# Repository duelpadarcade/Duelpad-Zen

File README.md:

## **Duelpad Zen**

Duelpad zen is a split-layout all-button controller, which is based on GP2040-CE projects. So it inherits the features, and is also added with something new.

## **Features**

- A navigating stick used with a humble UI,which can change the working status of the controller.
- Select from 13 input modes including X-Input, Nintendo Switch, Playstation 4/5, Xbox One, D-Input, and Keyboard
- Input latency average of 0.76ms in Xinput and 0.90ms for Playstation 5.
- Multiple SOCD cleaning modes - Up Priority (a.k.a. Stickless), Neutral, and Second Input Priority.
- Left and Right stick emulation via D-pad inputs as well as dedicated toggle switches.
- Dual direction via D-pad + LS/RS.
- Reversed input via a button.
- [Turbo and Turbo LED](https://gp2040-ce.info/add-ons/turbo) with selectable speed
- Per-button RGB LED support.
- PWM Player indicator LED support (XInput only).
- Multiple LED profiles support.
- Support for 128x64 monochrome I2C displays - SSD1306, SH1106, and SH1107 compatible.
- Custom startup splash screen and easy image upload via web configuration.
- Support for passive buzzer speaker (3v or 5v).
- [Built-in, embedded web configuration](https://gp2040-ce.info/web-configurator) - No download required!
- A bunch of RGB lights run by an extra MCU

## Support

We welcome anyone with ideas or issues to join us:

Official Website: www.duelpad.com

Discord Server:[DUELPAD](https://discord.gg/BXeWntUJ8B)

## Acknowledgements

This project is based on the excellent work of GP2040-CE team([Contributors to OpenStickCommunity/GP2040-CE · GitHub](https://github.com/OpenStickCommunity/GP2040-CE/graphs/contributors))

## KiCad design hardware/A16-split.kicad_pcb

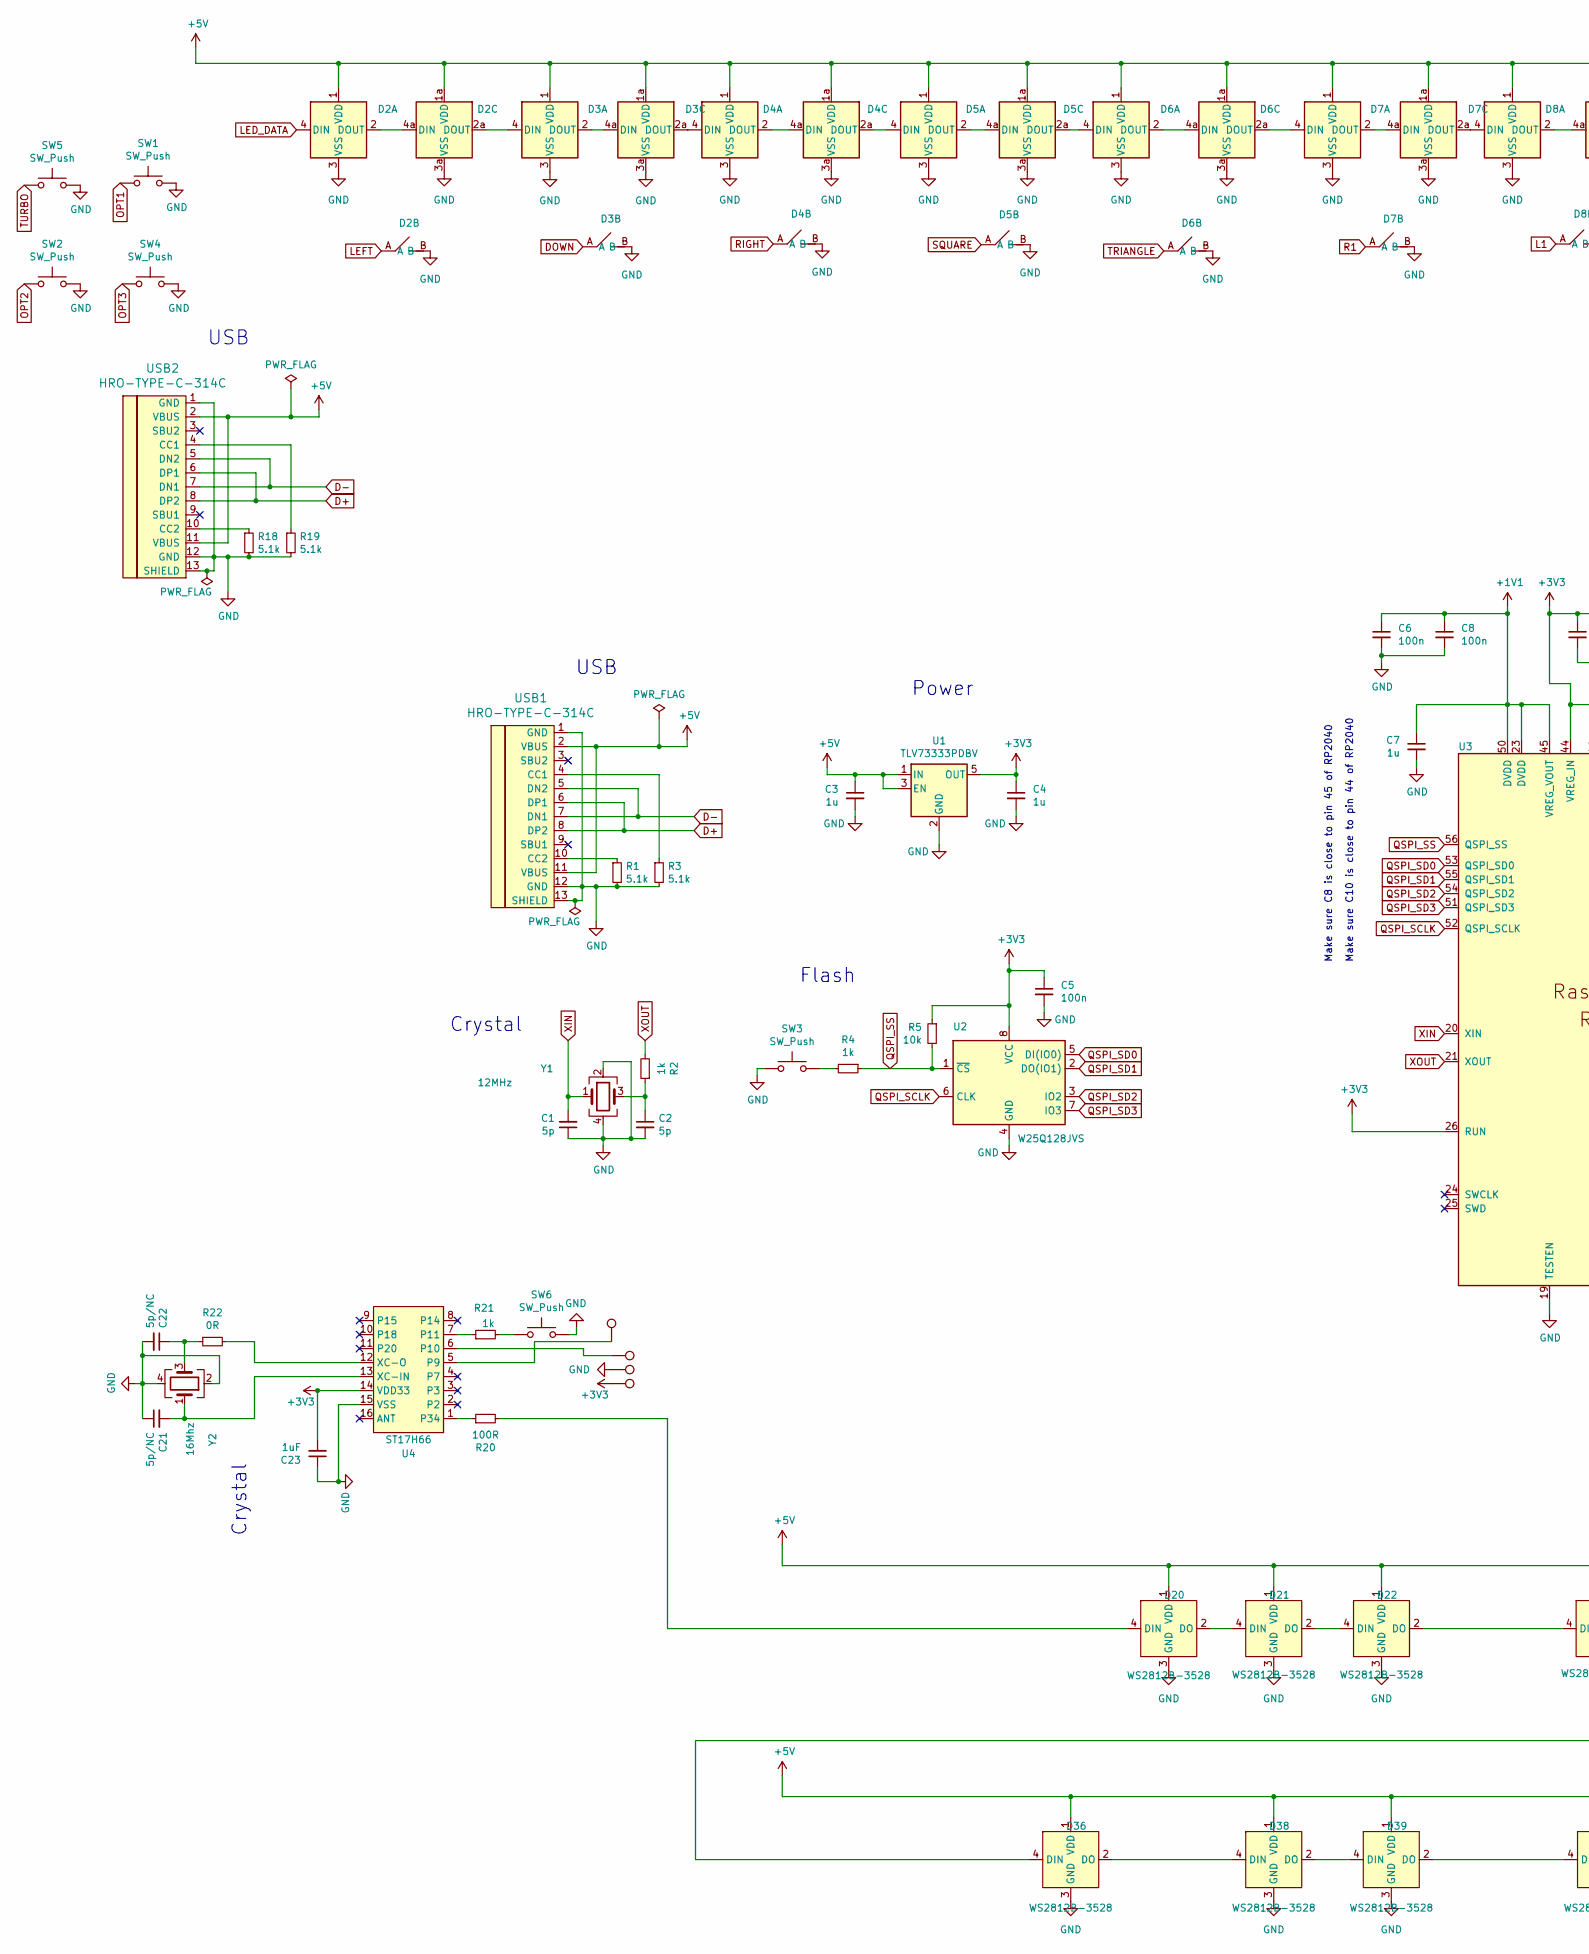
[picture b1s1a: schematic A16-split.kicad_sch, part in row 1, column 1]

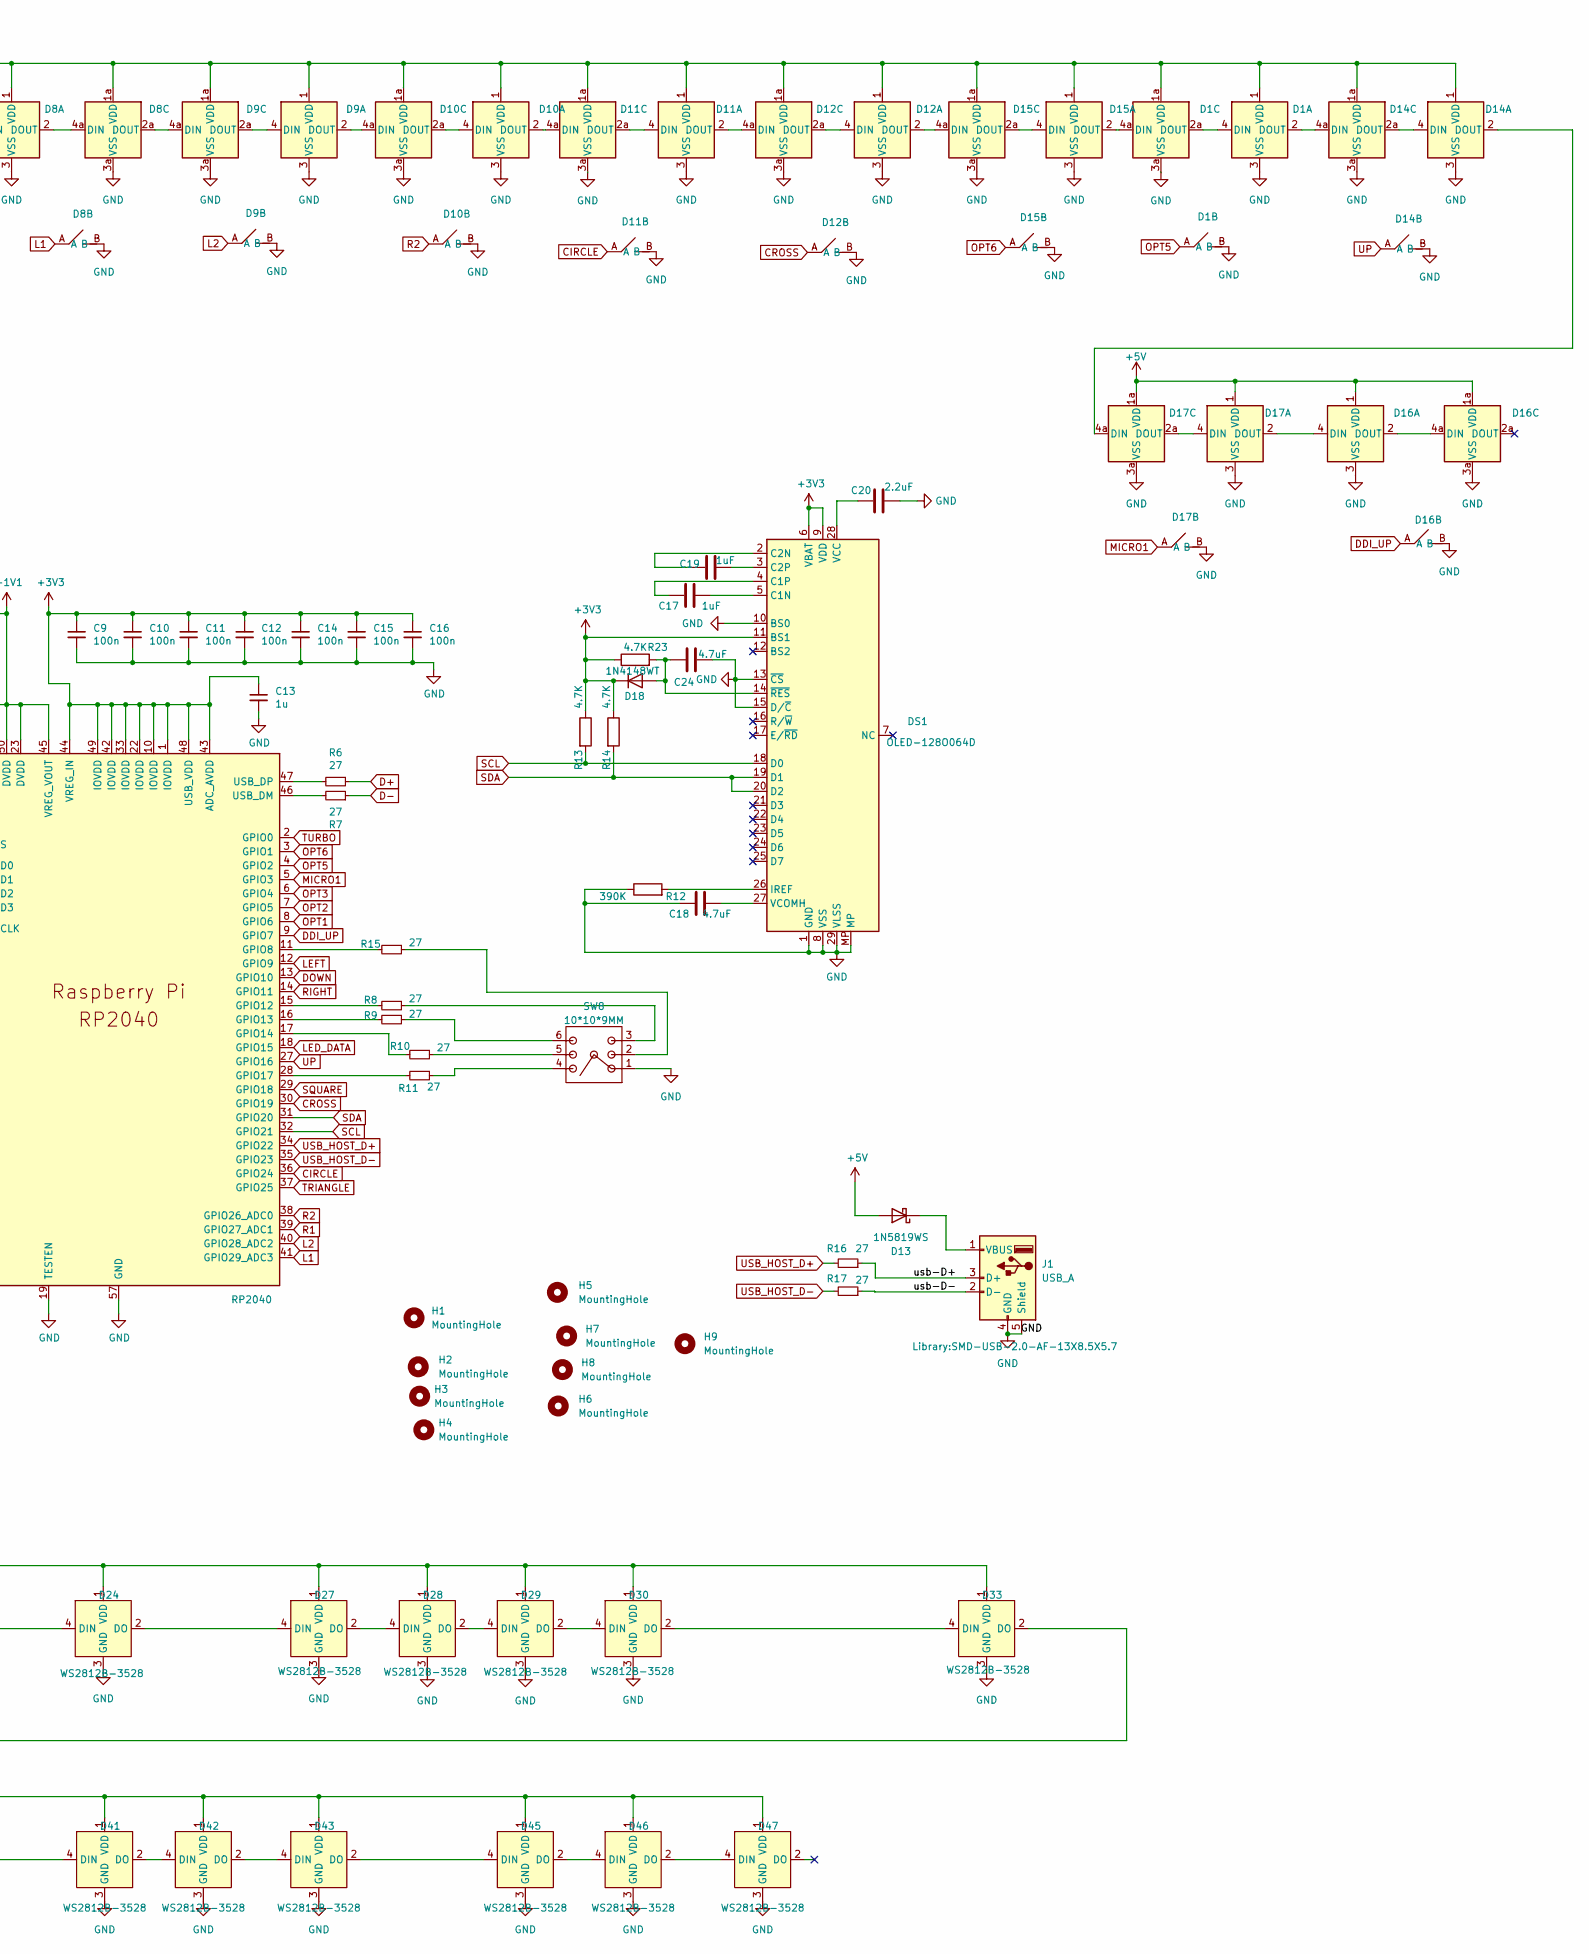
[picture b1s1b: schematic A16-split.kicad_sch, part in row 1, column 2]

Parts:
C1, C2: 5p; C_0402_1005Metric; LCSC C1570
C3, C4, C7, C13: 1u; C_0402_1005Metric; LCSC C52923
C5, C6, C8, C9, C10, C11, C12, C14, C15, C16: 100n; C_0402_1005Metric; LCSC C1525
C17, C19: 1uF; C_0402_1005Metric
C18, C24: 4.7uF; C_0603_1608Metric
C20: 2.2uF; C_0603_1608Metric
C21, C22: 5p/NC; C_0402_1005Metric; LCSC C1570
C23: 1uF; C_0402_1005Metric; LCSC C52923
D1, D2, D3, D4, D5, D6, D7, D8, D9, D10, D11, D12, D14, D15, D16, D17: GATERON_KB_HOTSWAP_WS2812B; gateron_Kailh_PG1353_2LED-5.1MM
D13: 1N5819WS; D_SOD-323
D18: 1N4148WT; D_SOD-523
D20, D21, D22, D24, D27, D28, D29, D30, D33, D36, D38, D39, D41, D42, D43, D45, D46, D47: WS2812B-3528; SMD-LED-WS2812B-3528
DS1: OLED-128O064D; Flatbox_OLED_096-1
H1, H2, H3, H4, H5, H6, H7, H8, H9: MountingHole; MountingHole_3.15mm_M6
J1: USB_A; SMD-USB-2.0-AF-13X8.5X5.7
R1, R3, R18, R19: 5.1k; R_0402_1005Metric; LCSC C25905
R2, R4, R21: 1k; R_0402_1005Metric; LCSC C11702
R5: 10k; R_0402_1005Metric; LCSC C25744
R6, R7, R8, R9, R10, R11, R15, R16, R17: 27; R_0402_1005Metric; LCSC C138021
R12: 390K; R_0402_1005Metric
R13, R14, R23: 4.7K; R_0402_1005Metric
R20: 100R; R_0402_1005Metric; LCSC C11702
R22: 0R; R_0402_1005Metric; LCSC C11702
SW1, SW2, SW4, SW5: SW_Push; SW_Push_1P1T_NO_6x6mm_H5mm
SW3, SW6: SW_Push; SW_Push_1P1T_NO_6x6mm_H5mm; LCSC C271750
SW8: 10*10*9MM; TSX103G901-10x10
TP1, TP2, TP3, TP4: TestPoint; TestPoint_Pad_D1.5mm
U1: TLV73333PDBV; SOT-23-5; LCSC C134139
U2: W25Q128JVS; SOIC-8_5.23x5.23mm_P1.27mm; LCSC C97521
U3: RP2040; RP2040-QFN-56; LCSC C2040
U4: ST17H66; TSSOP-16_4.4x5mm_P0.65mm
USB1, USB2: HRO-TYPE-C-314C; HRO-TYPE-MC-314C-4P16; LCSC C165948
Y1: 12MHz; Crystal_SMD_3225-4Pin_3.2x2.5mm; LCSC C9002
Y2: 16Mhz; Crystal_SMD_3225-4Pin_3.2x2.5mm; LCSC C9002

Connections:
+1V1: C6.1, C7.1, C8.1, U3.23 (DVDD), U3.45 (VREG_VOUT), U3.50 (DVDD)
+3V3: C4.1, C5.1, C9.1, C10.1, C11.1, C12.1, C13.1, C14.1, C15.1, C16.1, C23.2, D18.1 (K), DS1.6 (VBAT), DS1.9 (VDD), DS1.11 (BS1), R5.1, R13.1, R14.1, R23.1, TP4.1, U1.5 (OUT), U2.8 (VCC), U3.1 (IOVDD), U3.10 (IOVDD), U3.22 (IOVDD), U3.26 (RUN), U3.33 (IOVDD), U3.42 (IOVDD), U3.43 (ADC_AVDD), U3.44 (VREG_IN), U3.48 (USB_VDD), U3.49 (IOVDD), U4.14 (VDD33)
+5V: C3.1, D1.1 (VDD), D1.1a (VDD), D2.1 (VDD), D2.1a (VDD), D3.1 (VDD), D3.1a (VDD), D4.1 (VDD), D4.1a (VDD), D5.1 (VDD), D5.1a (VDD), D6.1 (VDD), D6.1a (VDD), D7.1 (VDD), D7.1a (VDD), D8.1 (VDD), D8.1a (VDD), D9.1 (VDD), D9.1a (VDD), D10.1 (VDD), D10.1a (VDD), D11.1 (VDD), D11.1a (VDD), D12.1 (VDD), D12.1a (VDD), D13.2 (A), D14.1 (VDD), D14.1a (VDD), D15.1 (VDD), D15.1a (VDD), D16.1 (VDD), D16.1a (VDD), D17.1 (VDD), D17.1a (VDD), D20.1 (VDD), D21.1 (VDD), D22.1 (VDD), D24.1 (VDD), D27.1 (VDD), D28.1 (VDD), D29.1 (VDD), D30.1 (VDD), D33.1 (VDD), D36.1 (VDD), D38.1 (VDD), D39.1 (VDD), D41.1 (VDD), D42.1 (VDD), D43.1 (VDD), D45.1 (VDD), D46.1 (VDD), D47.1 (VDD), U1.1 (IN), U1.3 (EN), USB1.2 (VBUS), USB1.11 (VBUS), USB2.2 (VBUS), USB2.11 (VBUS)
/usb-D+: J1.3 (D+), R16.1
/usb-D-: J1.2 (D-), R17.1
CIRCLE: D11.A, U3.36 (GPIO24)
CROSS: D12.A, U3.30 (GPIO19)
D+: R6.1, USB1.6 (DP1), USB1.8 (DP2), USB2.6 (DP1), USB2.8 (DP2)
D-: R7.1, USB1.5 (DN2), USB1.7 (DN1), USB2.5 (DN2), USB2.7 (DN1)
DDI_UP: D16.A, U3.9 (GPIO7)
DOWN: D3.A, U3.13 (GPIO10)
GND: C1.1, C2.2, C3.2, C4.2, C5.2, C6.2, C7.2, C8.2, C9.2, C10.2, C11.2, C12.2, C13.2, C14.2, C15.2, C16.2, C18.1, C20.2, C21.1, C22.2, C23.1, C24.2, D1.3 (VSS), D1.3a (VSS), D1.B, D2.3 (VSS), D2.3a (VSS), D2.B, D3.3 (VSS), D3.3a (VSS), D3.B, D4.3 (VSS), D4.3a (VSS), D4.B, D5.3 (VSS), D5.3a (VSS), D5.B, D6.3 (VSS), D6.3a (VSS), D6.B, D7.3 (VSS), D7.3a (VSS), D7.B, D8.3 (VSS), D8.3a (VSS), D8.B, D9.3 (VSS), D9.3a (VSS), D9.B, D10.3 (VSS), D10.3a (VSS), D10.B, D11.3 (VSS), D11.3a (VSS), D11.B, D12.3 (VSS), D12.3a (VSS), D12.B, D14.3 (VSS), D14.3a (VSS), D14.B, D15.3 (VSS), D15.3a (VSS), D15.B, D16.3 (VSS), D16.3a (VSS), D16.B, D17.3 (VSS), D17.3a (VSS), D17.B, D20.3 (GND), D21.3 (GND), D22.3 (GND), D24.3 (GND), D27.3 (GND), D28.3 (GND), D29.3 (GND), D30.3 (GND), D33.3 (GND), D36.3 (GND), D38.3 (GND), D39.3 (GND), D41.3 (GND), D42.3 (GND), D43.3 (GND), D45.3 (GND), D46.3 (GND), D47.3 (GND), DS1.1 (GND), DS1.8 (VSS), DS1.10 (BS0), DS1.13 (~CS), DS1.15 (D/~C), DS1.29 (VLSS), DS1.30 (GND), DS1.MP, J1.4 (GND), J1.5 (Shield), R1.2, R3.2, R12.1, R18.2, R19.2, SW1.2, SW2.2, SW3.1, SW4.2, SW5.2, SW6.2, SW8.1, TP3.1, U1.2 (GND), U2.4 (GND), U3.19 (TESTEN), U3.57 (GND), U4.15 (VSS), USB1.1 (GND), USB1.12 (GND), USB1.13 (SHIELD), USB2.1 (GND), USB2.12 (GND), USB2.13 (SHIELD), Y1.2, Y1.4, Y2.2, Y2.4
L1: D8.A, U3.41 (GPIO29_ADC3)
L2: D9.A, U3.40 (GPIO28_ADC2)
LED_DATA: D2.4 (DIN), U3.18 (GPIO15)
LEFT: D2.A, U3.12 (GPIO9)
MICRO1: D17.A, U3.5 (GPIO3)
unnamed: C2.1, R2.1, Y1.3
unnamed: C22.1, R22.1, Y2.3
unnamed: D1.2a (DOUT), D1.4 (DIN)
unnamed: D2.2 (DOUT), D2.4a (DIN)
unnamed: D2.2a (DOUT), D3.4 (DIN)
unnamed: D3.2 (DOUT), D3.4a (DIN)
unnamed: D3.2a (DOUT), D4.4 (DIN)
unnamed: D4.2 (DOUT), D4.4a (DIN)
unnamed: D4.2a (DOUT), D5.4 (DIN)
unnamed: D5.2 (DOUT), D5.4a (DIN)
unnamed: D5.2a (DOUT), D6.4 (DIN)
unnamed: D6.2 (DOUT), D6.4a (DIN)
unnamed: D6.2a (DOUT), D7.4 (DIN)
unnamed: D7.2 (DOUT), D7.4a (DIN)
unnamed: D7.2a (DOUT), D8.4 (DIN)
unnamed: D8.2 (DOUT), D8.4a (DIN)
unnamed: D8.2a (DOUT), D9.4a (DIN)
unnamed: D9.2a (DOUT), D9.4 (DIN)
unnamed: D10.2a (DOUT), D10.4 (DIN)
unnamed: D10.2 (DOUT), D11.4a (DIN)
unnamed: D9.2 (DOUT), D10.4a (DIN)
unnamed: D11.2a (DOUT), D11.4 (DIN)
unnamed: D11.2 (DOUT), D12.4a (DIN)
unnamed: D12.2a (DOUT), D12.4 (DIN)
unnamed: D12.2 (DOUT), D15.4a (DIN)
unnamed: D13.1 (K), J1.1 (VBUS)
unnamed: D14.2a (DOUT), D14.4 (DIN)
unnamed: D14.2 (DOUT), D17.4a (DIN)
unnamed: D1.2 (DOUT), D14.4a (DIN)
unnamed: D15.2a (DOUT), D15.4 (DIN)
unnamed: D1.4a (DIN), D15.2 (DOUT)
unnamed: D16.4 (DIN), D17.2 (DOUT)
unnamed: D16.2 (DOUT), D16.4a (DIN)
unnamed: D17.2a (DOUT), D17.4 (DIN)
unnamed: C24.1, D18.2 (A), DS1.14 (~RES), R23.2
unnamed: D20.4 (DIN), R20.2
unnamed: D20.2 (DO), D21.4 (DIN)
unnamed: D21.2 (DO), D22.4 (DIN)
unnamed: D22.2 (DO), D24.4 (DIN)
unnamed: D24.2 (DO), D27.4 (DIN)
unnamed: D27.2 (DO), D28.4 (DIN)
unnamed: D28.2 (DO), D29.4 (DIN)
unnamed: D29.2 (DO), D30.4 (DIN)
unnamed: D30.2 (DO), D33.4 (DIN)
unnamed: D33.2 (DO), D36.4 (DIN)
unnamed: D36.2 (DO), D38.4 (DIN)
unnamed: D38.2 (DO), D39.4 (DIN)
unnamed: D39.2 (DO), D41.4 (DIN)
unnamed: D41.2 (DO), D42.4 (DIN)
unnamed: D42.2 (DO), D43.4 (DIN)
unnamed: D43.2 (DO), D45.4 (DIN)
unnamed: D45.2 (DO), D46.4 (DIN)
unnamed: D46.2 (DO), D47.4 (DIN)
unnamed: C17.2, DS1.5 (C1N)
unnamed: C17.1, DS1.4 (C1P)
unnamed: C19.1, DS1.2 (C2N)
unnamed: C19.2, DS1.3 (C2P)
unnamed: DS1.26 (IREF), R12.2
unnamed: C20.1, DS1.28 (VCC)
unnamed: C18.2, DS1.27 (VCOMH)
unnamed: R4.2, SW3.2
unnamed: R8.1, SW8.3
unnamed: R9.1, SW8.6
unnamed: R10.1, SW8.5
unnamed: R11.1, SW8.4
unnamed: R15.1, SW8.2
unnamed: R21.2, SW6.1
unnamed: R15.2, U3.11 (GPIO8)
unnamed: R8.2, U3.15 (GPIO12)
unnamed: R9.2, U3.16 (GPIO13)
unnamed: R10.2, U3.17 (GPIO14)
unnamed: R11.2, U3.28 (GPIO17)
unnamed: R7.2, U3.46 (USB_DM)
unnamed: R6.2, U3.47 (USB_DP)
unnamed: TP1.1, U4.5 (P9)
unnamed: TP2.1, U4.6 (P10)
unnamed: R21.1, U4.7 (P11)
unnamed: R20.1, U4.1 (P34)
unnamed: C21.2, U4.13 (XC-IN), Y2.1
unnamed: R22.2, U4.12 (XC-O)
unnamed: R3.1, USB1.4 (CC1)
unnamed: R1.1, USB1.10 (CC2)
unnamed: R19.1, USB2.4 (CC1)
unnamed: R18.1, USB2.10 (CC2)
OPT1: SW1.1, U3.8 (GPIO6)
OPT2: SW2.1, U3.7 (GPIO5)
OPT3: SW4.1, U3.6 (GPIO4)
OPT5: D1.A, U3.4 (GPIO2)
OPT6: D15.A, U3.3 (GPIO1)
QSPI_SCLK: U2.6 (CLK), U3.52 (QSPI_SCLK)
QSPI_SD0: U2.5 (DI(IO0)), U3.53 (QSPI_SD0)
QSPI_SD1: U2.2 (DO(IO1)), U3.55 (QSPI_SD1)
QSPI_SD2: U2.3 (IO2), U3.54 (QSPI_SD2)
QSPI_SD3: U2.7 (IO3), U3.51 (QSPI_SD3)
QSPI_SS: R4.1, R5.2, U2.1 (~CS), U3.56 (QSPI_SS)
R1: D7.A, U3.39 (GPIO27_ADC1)
R2: D10.A, U3.38 (GPIO26_ADC0)
RIGHT: D4.A, U3.14 (GPIO11)
SCL: DS1.18 (D0), R13.2, U3.32 (GPIO21)
SDA: DS1.19 (D1), DS1.20 (D2), R14.2, U3.31 (GPIO20)
SQUARE: D5.A, U3.29 (GPIO18)
TRIANGLE: D6.A, U3.37 (GPIO25)
TURBO: SW5.1, U3.2 (GPIO0)
UP: D14.A, U3.27 (GPIO16)
USB_HOST_D+: R16.2, U3.34 (GPIO22)
USB_HOST_D-: R17.2, U3.35 (GPIO23)
XIN: C1.2, U3.20 (XIN), Y1.1
XOUT: R2.2, U3.21 (XOUT)

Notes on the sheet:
USB
Make sure C10 is close to pin 44 of RP2040
Crystal
Flash
Power
Make sure C8 is close to pin 45 of RP2040

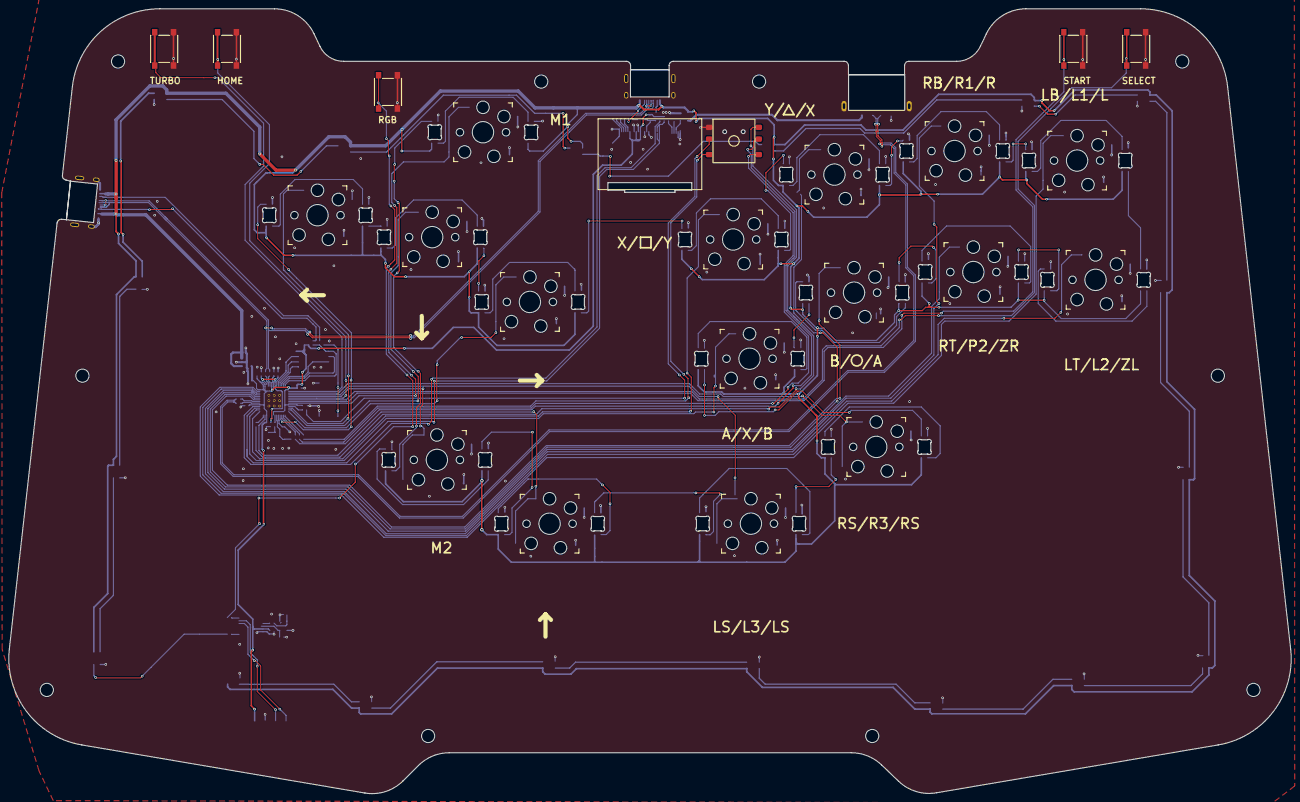
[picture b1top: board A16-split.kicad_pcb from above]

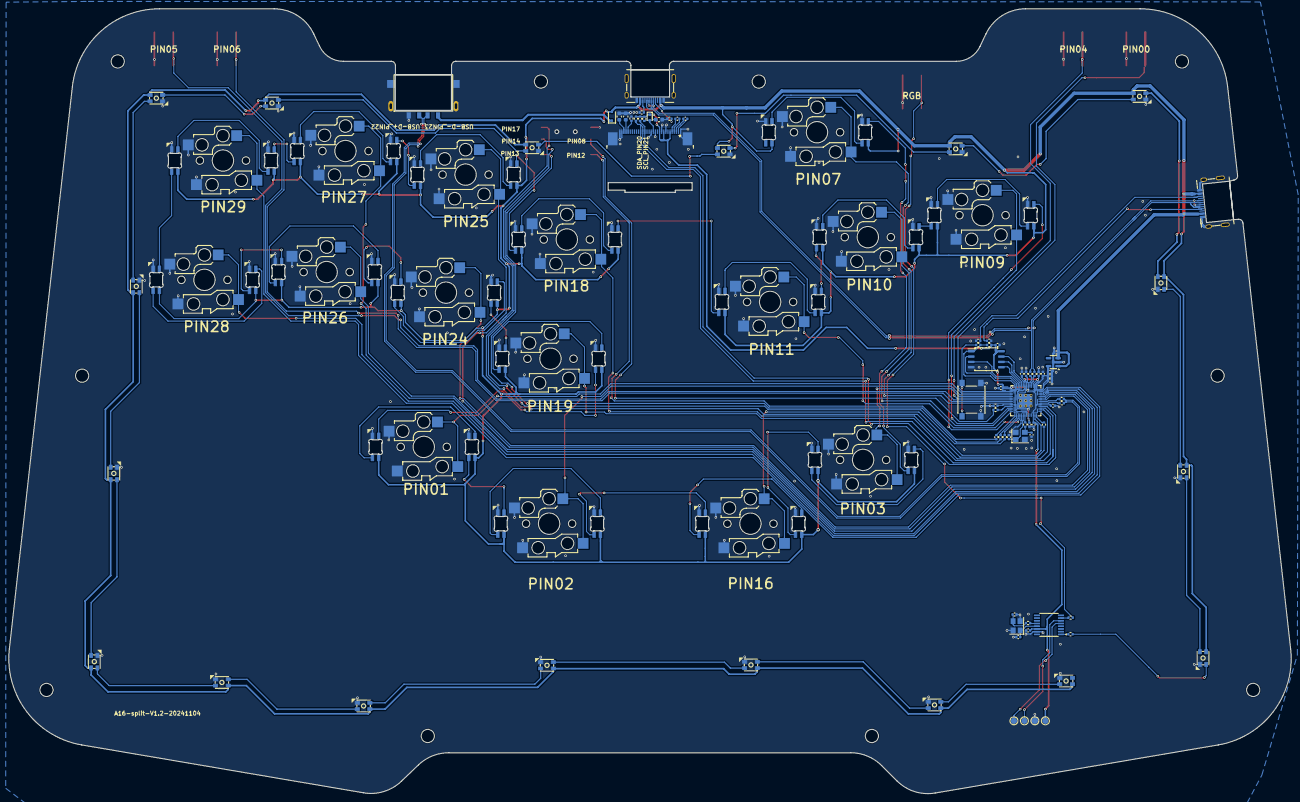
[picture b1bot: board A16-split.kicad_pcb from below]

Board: 2 copper layers, 306.1 x 187.3 mm, 114 parts (81 on the bottom side), 125 nets.

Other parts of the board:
H9#2: MountingHole; MountingHole_3.15mm_M6

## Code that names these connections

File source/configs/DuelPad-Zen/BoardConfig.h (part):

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#define GPIO_PIN_10 GpioAction::BUTTON_PRESS_DOWN   // DOWN   | DOWN   | DOWN    | DOWN     | DOWN   | DOWN   |
#define GPIO_PIN_11 GpioAction::BUTTON_PRESS_RIGHT  // RIGHT  | RIGHT  | RIGHT   | RIGHT    | RIGHT  | RIGHT  |
#define GPIO_PIN_09 GpioAction::BUTTON_PRESS_LEFT   // LEFT   | LEFT   | LEFT    | LEFT     | LEFT   | LEFT   |
#define GPIO_PIN_19 GpioAction::BUTTON_PRESS_B1     // B1     | A      | B       | Cross    | 2      | K1     |
#define GPIO_PIN_24 GpioAction::BUTTON_PRESS_B2     // B2     | B      | A       | Circle   | 3      | K2     |
#define GPIO_PIN_26 GpioAction::BUTTON_PRESS_R2     // R2     | RT     | ZR      | R2       | 8      | K3     |
#define GPIO_PIN_28 GpioAction::BUTTON_PRESS_L2     // L2     | LT     | ZL      | L2       | 7      | K4     |
#define GPIO_PIN_18 GpioAction::BUTTON_PRESS_B3     // B3     | X      | Y       | Square   | 1      | P1     |
#define GPIO_PIN_25 GpioAction::BUTTON_PRESS_B4     // B4     | Y      | X       | Triangle | 4      | P2     |
#define GPIO_PIN_27 GpioAction::BUTTON_PRESS_R1     // R1     | RB     | R       | R1       | 6      | P3     |
#define GPIO_PIN_29 GpioAction::BUTTON_PRESS_L1     // L1     | LB     | L       | L1       | 5      | P4     |
#define GPIO_PIN_05 GpioAction::BUTTON_PRESS_S1     // S1     | Back   | Minus   | Select   | 9      | Coin   |
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#define KEY_DPAD_DOWN   HID_KEY_ARROW_DOWN    // DOWN   | DOWN   | DOWN    | DOWN     | DOWN   | DOWN   |
#define KEY_DPAD_RIGHT  HID_KEY_ARROW_RIGHT   // RIGHT  | RIGHT  | RIGHT   | RIGHT    | RIGHT  | RIGHT  |
#define KEY_DPAD_LEFT   HID_KEY_ARROW_LEFT    // LEFT   | LEFT   | LEFT    | LEFT     | LEFT   | LEFT   |
#define KEY_BUTTON_B1   HID_KEY_SHIFT_LEFT    // B1     | A      | B       | Cross    | 2      | K1     |
#define KEY_BUTTON_B2   HID_KEY_Z             // B2     | B      | A       | Circle   | 3      | K2     |
#define KEY_BUTTON_R2   HID_KEY_X             // R2     | RT     | ZR      | R2       | 8      | K3     |
#define KEY_BUTTON_L2   HID_KEY_V             // L2     | LT     | ZL      | L2       | 7      | K4     |
#define KEY_BUTTON_B3   HID_KEY_CONTROL_LEFT  // B3     | X      | Y       | Square   | 1      | P1     |
#define KEY_BUTTON_B4   HID_KEY_ALT_LEFT      // B4     | Y      | X       | Triangle | 4      | P2     |
#define KEY_BUTTON_R1   HID_KEY_SPACE         // R1     | RB     | R       | R1       | 6      | P3     |
#define KEY_BUTTON_L1   HID_KEY_C             // L1     | LB     | L       | L1       | 5      | P4     |
#define KEY_BUTTON_S1   HID_KEY_5             // S1     | Back   | Minus   | Select   | 9      | Coin   |
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
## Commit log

2024-11-13 README.md
2024-11-13 Create test
2024-11-22 update 3D/duelpad-zen
2024-11-22 Create LICENSE

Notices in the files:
source/configs/DuelPad-Zen/BoardConfig.h:
SPDX-License-Identifier: MIT
SPDX-FileCopyrightText: Copyright (c) 2021 Jason Skuby (mytechtoybox.com)
